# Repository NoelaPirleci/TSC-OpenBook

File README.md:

# TSC-OpenBook
# Descriere funcționalitate hardware

Proiectul se bazează pe microcontroller-ul **ESP32-C6**, care gestionează comunicarea cu toate componentele externe și senzorii conectați. Acest microcontroller oferă conectivitate **Wi-Fi** și **Bluetooth**, dar și suport pentru interfetele **SPI**, **I2C** și **UART**. Este conectat la 3V3 printr-un regulator de tensiune **LDO**, care primește energie de la o baterie **Li-Po** de 3.7V. 

Afisarea informațiilor se face utilizând un **display E-Paper** conectat prin **interfața SPI**, care are un consum redus de energie, fiind activ doar la actualizările ecranului. Informațiile afișate vor include data, ora, valorile senzorilor etc. 

Monitorizarea mediului se face cu ajutorul senzorului **BME688**, care măsoară temperatura, umiditatea și presiunea atmosferică, comunicând cu microcontroller-ul prin magistrala **I2C**. Modulul **RTC DS3231** este conectat și el la I2C și menține ora și data exactă, chiar și atunci când sistemul este oprit.

Prin **portul USB-C** se face alimentarea sistemului, care este conectat la circuitul de încărcare a bateriei utilizând **MCP73831**. Acesta controlează încărcarea bateriei Li-Po. Tensiunea va fi stabilită la **3.3V** pentru alimentarea senzorilor și a microcontroller-ului. Circuitul **MAX17048** este folosit pentru a monitoriza nivelul încărcării bateriei și furnizează informații despre tensiune și starea de încărcare prin I2C.

Consumul de energie este gestionat de ESP32-C6, care poate intra în **modul de consum redus**, permițând o durată lungă de viață a bateriei. Consumul în regim activ variază în funcție de sarcinile și componentele active în acel moment.

Pentru stocare, sistemul va folosi o **memorie externă NOR Flash**, conectată prin **SPI**, dar va exista și un slot pentru **card SD**, care va fi folosit pentru a loga local datele. Butoanele sunt conectate la **GPIO-uri** și vor fi folosite pentru resetare, bootare și alte acțiuni.

---

# Schema bloc

# Descriere pini ESP32-C6

Pinii microcontroller-ului **ESP32-C6** sunt utilizați în cadrul a cinci categorii:

## 1. Interfața SPI
Este folosită pentru comunicarea componentelor care necesită viteze mari de transfer. Pinii utilizați sunt:
- **IO0**: linia **MOSI** unde microcontroller-ul va trimite date către perifericele SPI.
- **IO1**: linia **MISO** unde ESP32-C6 va primi date de la cardul SD.
- **IO2**: linia **SCK** care va genera semnalul de ceas pentru sincronizarea SPI.
- **IO3**: linia **CS** pentru memoria **Flash NOR**.
- **IO4**: linia **CS** pentru display-ul **E-paper**.
- **IO5**: linia **CS** pentru slotul de card **SD**.
- **IO6, IO7, IO8**: pentru semnalele de control ale **E-Paper**-ului: **reset**, **busy**, **data/command (DC)**. Acești pini sunt utilizați pentru a evita conflictele cu alte interfețe și permit o rutare eficientă a traseelor pe placă.

## 2. Interfața I2C
Este folosită pentru a conecta senzorii de mediu și circuitele de monitorizare a tensiunii sau a timpului. Această interfață va conecta componentele: **BME688**, **MAX17048**, **DS3231**. Pinii folosiți sunt:
- **IO15**: linia **SCL**, folosită pentru semnalul de ceas.
- **IO16**: linia **SDA**, care va transmite date bidirecțional între microcontroller și perifericele I2C. Acești pini sunt aleși pentru a nu se suprapune cu cei de la SPI sau UART și pentru a permite extinderea prin **Qwiic**.

## 3. Interfața UART
Este folosită pentru **debugging**, comunicare serială sau conectare la module externe. Pinii utilizați sunt:
- **IO17**: **TXD**, linia de ieșire a datelor de la ESP32 către PC sau consolă.
- **IO18**: **RXD**, linia de intrare a datelor către ESP32. Acești pini sunt utili în faza de dezvoltare pentru testare, dar pot fi folosiți și în aplicațiile finale, dacă UART nu este necesar.

## 4. Pini GPIO
Sunt folosiți pentru butoanele **boot**, **reset** sau **change**. Pinii utilizați sunt:
- **IO9**: este folosit pentru **BOOT** și permite intrarea în modul de programare.
- **EN**: este pinul hardware **RESET** al ESP32-C6.
- **IO10, IO11**: sunt utilizați pentru butoane suplimentare, care au diverse acțiuni în aplicație. Acești pini au fost aleși pentru că sunt disponibili în schema de referință ESP32-C6 și nu sunt partajați cu perifericele.

## 5. Alimentare
Pinii de alimentare sunt:
- **3V3**: este intrarea de alimentare stabilizată la 3.3V, provenind din regulatorul LDO alimentat de la bateria **Li-Po**.
- **GND**: conexiunea de masă.

# Bill of Materials

| CNT | VAL | Device | Package | Parts | PURCHASE | DATASHEET |
| --- | ----- | ------ | ------- | ----- | ------------ | ------------- |
| 1 |  | ADAFRUIT_LEDCHIP-LED0603 | 0603 | CHG_LED | https://www.digikey.com/en/products/detail/w%C3%BCrth-elektronik/150060RS75000/4489901 | https://www.we-online.com/components/products/datasheet/150060RS75000.pdf |
| 1 | 0.1uF/50V | ESP32_WROVER_EAGLE-LTSPICE_C0402 | 0402 | EPD_C3 | https://www.digikey.com/en/products/detail/samsung-electro-mechanics/CL05B104KB5NNNC/11696318 | https://weblib.samsungsem.com/mlcc/mlcc-ec-data-sheet.do?partNumber=CL05B104KB5NNN |
| 1 | 0.47 | ESP32_WROVER_EAGLE-LTSPICE_RR0402 | 0402 | R3 | https://www.digikey.com/en/products/detail/panasonic-electronic-components/ERJ-2BQJR47X/5647384 | https://industrial.panasonic.com/cdbs/www-data/pdf/RDN0000/AOA0000C313.pdf |
| 1 | 100K | ESP32_WROVER_EAGLE-LTSPICE_RR0402 | 0402 | R_PWRUSB | https://www.digikey.com/en/products/detail/panasonic-electronic-components/ERJ-2RKF1003X/192081 | https://industrial.panasonic.com/cdbs/www-data/pdf/RDA0000/AOA0000C304.pdf |
| 8 | 100nF | ESP32_WROVER_EAGLE-LTSPICE_C0402 | 0402 | C1, C2, C3_USB, C5, C7, C8, C9, C_DELAY | https://www.digikey.com/en/products/detail/samsung-electro-mechanics/CL05B104KP5NNNC/3886660 | https://mm.digikey.com/Volume0/opasdata/d220001/medias/docus/609/CL05B104KP5NNNC_Spec.pdf |
| 1 | 100uF | RCL_CPOL-EUCT3528 | 3528 | C_TANT | https://ro.mouser.com/ProductDetail/KEMET/T491B107M006AT?qs=U312oeP%2FpiHOgyk6KO2m0g%3D%3D | https://ro.mouser.com/datasheet/2/447/KEM_T2005_T491-3316937.pdf
| 16 | 10K | ESP32_WROVER_EAGLE-LTSPICE_RR0402 | 0402 | R1, R1_PINH1, R1_PINH2, R2-PINH1, R2_PINH2, R4, R5, R6, R7, R8, R9, R10, R_BOOT, R_CHANGE, R_CL1, R_RESET | https://www.digikey.com/en/products/detail/panasonic-electronic-components/ERJ-2RKF1002X/192073 | https://industrial.panasonic.com/cdbs/www-data/pdf/RDA0000/AOA0000C304.pdf |
| 1 | 10uF | ESP32_WROVER_EAGLE-LTSPICE_C0402 | 0402 | C6 | https://www.digikey.com/en/products/detail/samsung-electro-mechanics/CL05A106MP5NUNC/3887108 | https://mm.digikey.com/Volume0/opasdata/d220001/medias/docus/2614/CL05A106MP5NUNC_Spec.pdf |
| 1 | 112A-TAAR-R03_ATTEND | 112A-TAAR-R03_ATTEND |  | J4 | https://www.digikey.ro/en/products/detail/attend-technology/112A-TAAR-R03/17633923 | https://www.attend.com.tw/data/download/file/112A-TAAR-R03_Spec.pdf |
| 1 | 15 | ESP32_WROVER_EAGLE-LTSPICE_RR0402 | 0402 | R_CAPACITOR | https://www.digikey.com/en/products/detail/panasonic-electronic-components/ERJ-2RKF15R0X/192142 | https://industrial.panasonic.com/cdbs/www-data/pdf/RDA0000/AOA0000C304.pdf |
| 1 | 1uF | ESP32_WROVER_EAGLE-LTSPICE_C0402 | 0402 | C4 | https://www.digikey.com/en/products/detail/samsung-electro-mechanics/CL05A105KO5NNNC/3886725 | https://mm.digikey.com/Volume0/opasdata/d220001/medias/docus/609/CL05A105KO5NNNC_Spec_5-2-19.pdf |
| 9 | 1uF/50V | ESP32_WROVER_EAGLE-LTSPICE_C0402 | 0402 | EPD_C1, EPD_C2, EPD_C4, EPD_C5, EPD_C6, EPD_C7, EPD_C8, EPD_C9, EPD_C10 | https://www.digikey.com/en/products/detail/murata-electronics/GRM155R61H105KE05D/13531808 | https://search.murata.co.jp/Ceramy/image/img/A01X/G101/ENG/GRM155R61H105KE05-01A.pdf |
| 1 | 2.2 | ESP32_WROVER_EAGLE-LTSPICE_RR0402 | 0402 | R2 | https://www.digikey.com/en/products/detail/panasonic-electronic-components/ERJ-2GEJ2R2X/282078 | https://api.pim.na.industrial.panasonic.com/file_stream/main/fileversion/1242 |
| 1 | 200 | ESP32_WROVER_EAGLE-LTSPICE_RR0402 | 0402 | R1_BAT | https://www.digikey.com/en/products/detail/panasonic-electronic-components/ERJ-2RKF2000X/192215 | https://industrial.panasonic.com/cdbs/www-data/pdf/RDA0000/AOA0000C304.pdf |
| 2 | 20V/4.2A/52mO/1.4W | ESP32_WROVER_SPARKFUN-DISCRETESEMI_MOSFET_PCH-DMG2305UX-7 |  | Q1, Q2 | https://www.digikey.ro/en/products/detail/diodes-incorporated/DMG2305UX-7/4340667 | https://www.diodes.com/assets/Datasheets/DMG2305UX.pdf |
| 1 | 2K | ESP32_WROVER_EAGLE-LTSPICE_RR0402 | 0402 | R2_BAT | https://www.digikey.com/en/products/detail/panasonic-electronic-components/ERJ-2RKF2001X/192194 | https://industrial.panasonic.com/cdbs/www-data/pdf/RDA0000/AOA0000C304.pdf |
| 5 | 4.7uF | ESP32_WROVER_EAGLE-LTSPICE_C0402 | 0402 | C1_BAT, C1_BAT1, C2_BAT, C2_BAT1, C4_USB | https://www.digikey.com/en/products/detail/samsung-electro-mechanics/CL05A475KQ5NRNC/3887139 | https://mm.digikey.com/Volume0/opasdata/d220001/medias/docus/41/CL05A475KQ5NRNC_Spec.pdf |
| 1 | 4.7uF/25V | ESP32_WROVER_EAGLE-LTSPICE_C0402 | 0402 | C3 | https://www.digikey.com/en/products/detail/murata-electronics/GRM155C61E475ME15D/16821133 | https://search.murata.co.jp/Ceramy/image/img/A01X/G101/ENG/GRM155C61E475ME15-01A.pdf |
| 2 | 5k1 | ESP32_WROVER_EAGLE-LTSPICE_RR0402 | 0402 | R1_USB, R2_USB | https://www.digikey.com/en/products/detail/panasonic-electronic-components/ERJ-2GEJ512X/147044 | https://api.pim.na.industrial.panasonic.com/file_stream/main/fileversion/1242 |
| 1 | 68uH | 744043680IND_4828-WE-TPC_WRE |  | L1 | https://www.digikey.de/en/products/detail/w%C3%BCrth-elektronik/744043680/1638515?srsltid=AfmBOoreM6iTR1zfidcAYx5855uFKN_t-1dK5Y4hJLHk64FUsesZV3qH | https://www.we-online.com/components/products/datasheet/744043680.pdf |
| 1 | BD5229G-TR | BD5229G-TR |  | U6 | https://www.digikey.com/en/products/detail/rohm-semiconductor/BD5229G-TR/658502 | https://www.rohm.com/datasheet?p=BD5229G&dist=Digi-key&media=referral&source=digi-key.com&campaign=Digi-key |
| 1 | BME688 | ESP32_WROVER_BME680_BME680 |  | U8 | https://www.digikey.ro/en/products/detail/bosch-sensortec/BME688/13681261 | https://www.bosch-sensortec.com/media/boschsensortec/downloads/datasheets/bst-bme688-ds000.pdf |
| 3 | BUTTON_CUSYOMV1 | BUTTON_CUSYOMV1 |  | BOOT_BUTTON, CHANGE_BUTTON, RESET_BUTTON |  |  |
| 1 | CPH3225A | CPH3225A |  | C_SUPERCAP | https://www.digikey.com/en/products/detail/seiko-instruments/CPH3225A/8692444 | https://mm.digikey.com/Volume0/opasdata/d220001/medias/docus/6537/rev05-CPHCPM.pdf |
| 1 | DS3231SN# | DS3231SN# |  | U3 | https://www.digikey.com/en/products/detail/analog-devices-inc-maxim-integrated/DS3231SN/1197576 | https://www.analog.com/media/en/technical-documentation/data-sheets/DS3231.pdf |
| 1 | ESP32-C6-WROOM-1-N8 | ESP32-C6-WROOM-1-N8 |  | U1 | https://www.digikey.com/en/products/detail/espressif-systems/ESP32-C6-WROOM-1-N8/17728866 | https://www.espressif.com/sites/default/files/documentation/esp32-c6-wroom-1_wroom-1u_datasheet_en.pdf |
| 1 | ESP32C6_VARISTORCN1812 | ESP32C6_VARISTORCN1812 |  | PFMF.050.1 | https://www.digikey.com/en/products/detail/schurter-inc/PFMF-050-2/1731348 | https://us.schurter.com/en/datasheet/typ_PFMF.pdf |
| 2 | ESP32_WROVER_AVX---SD0805S020S1R0 | ESP32_WROVER_AVX---SD0805S020S1R0 |  | D2, D7 | https://www.digikey.gr/en/products/detail/kyocera-avx/SD0805S020S1R0/3749517 | https://datasheets.kyocera-avx.com/schottky.pdf |
| 1 | FH34SRJ-24S-0.5SH_99_ | FH34SRJ-24S-0.5SH_99_ |  | J1 | https://www.digikey.com/en/products/detail/hirose-electric-co-ltd/FH34SRJ-24S-0-5SH-99/5132529 | https://www.hirose.com/en/product/document?clcode=CL0580-1253-0-99&productname=FH34SRJ-12S-0.5SH(99)&series=FH34SRJ&documenttype=SpecSheet&lang=en&documentid=0000414526 |
| 1 | MAX17048G+T10 | MAX17048G+T10 |  | U2 | https://www.digikey.com/en/products/detail/analog-devices-inc-maxim-integrated/MAX17048G-T10/3758921 | https://datasheets.maximintegrated.com/en/ds/MAX17048-MAX17049.pdf |
| 3 | MBR0530 | MBR0530 |  | D3, D4, D5 | https://eu.mouser.com/ProductDetail/Micro-Commercial-Components-MCC/MBR0530-TP?qs=KFo7JewZbUECRHkxGanrdg%3D%3D&srsltid=AfmBOopI5EY-Qmh6fu8QJtXckZ14Imu1WB2G5-0En3D3mZ6aqi4jmsQ2 | https://eu.mouser.com/datasheet/2/258/MBR0520_MBR0580_SOD123_-2492194.pdf |
| 1 | MCP73831 | ESP32_WROVER_SPARKFUN-IC-POWER_MCP73831 |  | U7 | https://www.digikey.com/en/products/detail/microchip-technology/MCP73831T-2ACI-OT/964301 | https://ww1.microchip.com/downloads/en/DeviceDoc/MCP73831-Family-Data-Sheet-DS20001984H.pdf |
| 6 | PGB1010603MR | PGB1010603MR |  | D6, D8, D9, D10, D11, D12 | https://www.digikey.com/en/products/detail/littelfuse-inc/PGB1010603MR/715755 | https://www.littelfuse.com/assetdocs/pulseguard-esd-suppressors-pgb1-datasheet?assetguid=8a337998-d54d-466b-be4e-dc5bcd1f9321 |
| 1 | QWIIC_RIGHT_ANGLE | QWIIC_CONNECTORJS-1MM |  | J3 | https://www.sparkfun.com/qwiic-jst-connector-smd-4-pin-horizontal.html | https://cdn.sparkfun.com/assets/parts/1/2/2/8/9/Qwiic_Connector_Datasheet.pdf |
| 1 | SAMACSYS_PARTS_USB4110-GF-A | SAMACSYS_PARTS_USB4110-GF-A |  | J2 | https://www.digikey.ro/en/products/detail/gct/USB4110-GF-A/10384547 | https://gct.co/files/specs/usb4110-spec.pdf?v=6b2a6292-70a5-4bd5-a7e5-0f3fe03e015f |
| 1 | SI1308EDL-T1-GE3 | SI1308EDL-T1-GE3 |  | Q3 | https://www.digikey.com/en/products/detail/vishay-siliconix/SI1308EDL-T1-GE3/4876435 | https://www.vishay.com/docs/63399/si1308edl.pdf |
| 1 | USBLC6-2SC6Y | USBLC6-2SC6Y |  | D1 | https://www.digikey.com/en/products/detail/stmicroelectronics/USBLC6-2SC6Y/2819177 | https://www.st.com/content/ccc/resource/technical/document/datasheet/group0/94/15/6c/58/ba/91/46/42/DM00055262/files/DM00055262.pdf/jcr:content/translations/en.DM00055262.pdf |
| 1 | W25Q512JVEIQ | W25Q512JVEIQ |  | U4 | https://www.digikey.com/en/products/detail/winbond-electronics/W25Q512JVEIQ/10244706 | https://www.winbond.com/resource-files/W25Q512JV%20SPI%20RevB%2006252019%20KMS.pdf |
| 1 | XC6220A331MR-G | XC6220A331MR-G |  | U5 | https://www.digikey.in/en/products/detail/torex-semiconductor-ltd/XC6220A331MR-G/10165775 | https://product.torexsemi.com/system/files/series/xc6220.pdf |

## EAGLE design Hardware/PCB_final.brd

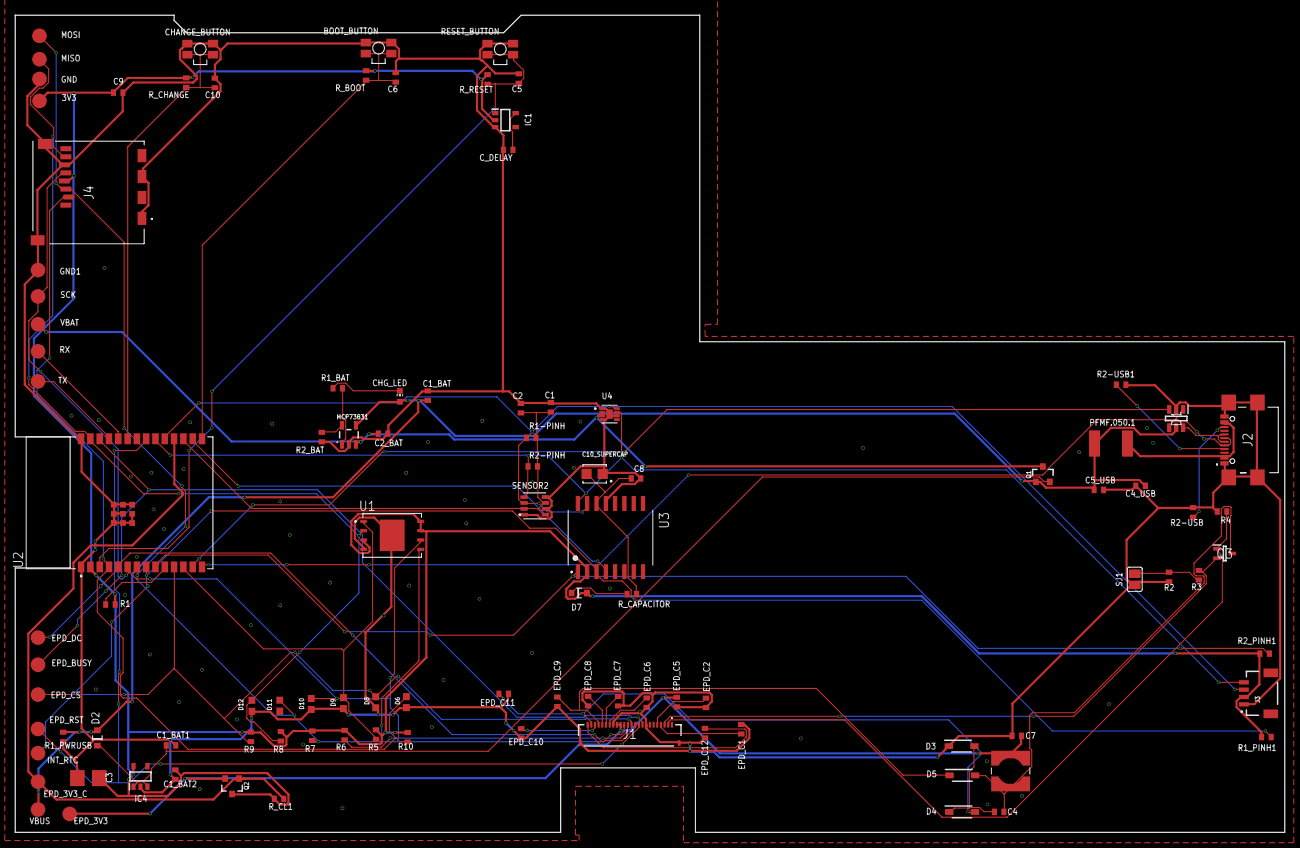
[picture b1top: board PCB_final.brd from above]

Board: 2 copper layers, 173.4 x 111.6 mm, 103 parts (0 on the bottom side), 55 nets.

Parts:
3V3: TPMODEL; TP20R
BOOT_BUTTON: BUTTON_CUSYOMV1BUTON; MYBUTTON
C1, C2, C4_USB, C6, C8, C9, C10: 100nF; ESP32_WROVER_EAGLE-LTSPICE_C0402
C1_BAT, C1_BAT1, C1_BAT2, C2_BAT, C5_USB: 4.7uF; ESP32_WROVER_EAGLE-LTSPICE_C0402
C3: 100uF TANT; RCL_CT3528
C4: 4.7uF/25V; ESP32_WROVER_EAGLE-LTSPICE_C0402
C5: 1uF; ESP32_WROVER_EAGLE-LTSPICE_C0402
C7: 10uF; ESP32_WROVER_EAGLE-LTSPICE_C0402
C10_SUPERCAP: CPH3225ASUPERCAP; CAPCP3225X100N
CHANGE_BUTTON: BUTTON_CUSYOMV1BUTON; MYBUTTON
CHG_LED: ADAFRUIT_CHIP-LED0603
C_DELAY: 100nF; ESP32_WROVER_EAGLE-LTSPICE_C0402
D1: USBLC6-2SC6YUSBL; SOT95P280X145-6N
D2, D7: ESP32_WROVER_AVX---SD0805S020S1R0_AVX_SD0805S020S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; ESP32_WROVER_AVX---SD0805S020S1R0_AVX_SD0805S020S1R0_0
D3, D4, D5: MBR0530MBR; SOD3716X135N
D6, D8, D9, D10, D11, D12: PGB1010603MRDIOC; DIOC1608X36N
EPD_3V3, EPD_3V3_C: TPMODEL; TP20R
EPD_BUSY: TPMODEL; TP20R
EPD_C1, EPD_C2, EPD_C5, EPD_C6, EPD_C7, EPD_C8, EPD_C9, EPD_C10, EPD_C11, EPD_C12: 1uF/50V; ESP32_WROVER_EAGLE-LTSPICE_C0402
EPD_CS: TPMODEL; TP20R
EPD_DC: TPTP20R; TP20R
EPD_RST: TPMODEL; TP20R
GND, GND1: TPTP20R; TP20R
IC1: BD5229G-TRBD5229; SOT95P280X125-5N
IC4: XC6220A331MR-G; SOT95P280X120-5N
INT_RTC: TPMODEL; TP20R
J1: FH34SRJ-24S-0.5SH_99_FH34; FH34SRJ24S05SH99
J2: SAMACSYS_PARTS_USB4110-GF-AUSB; SAMACSYS_PARTS_USB4110GFA
J3: QWIIC_RIGHT_ANGLE; JST04_1MM_RA
J4: 112A-TAAR-R03_ATTENDSDCARD; 112ATAARR03ATTEND
L1: 68uH; IND_4828-WE-TPC_WRE
MCP73831: ESP32_WROVER_SPARKFUN-IC-POWER_MCP73831ICPOWER; ESP32_WROVER_SPARKFUN-IC-POWER_SOT23-5
MISO: TPTP20R; TP20R
MOSI: TPMODEL; TP20R
PFMF.050.1: ESP32C6_VARISTOR; ESP32C6_VARISTOR_CT/CN1812
Q1, Q2: 20V/4.2A/52mΩ/1.4W; ESP32_WROVER_SPARKFUN-DISCRETESEMI_SOT23-3
Q3: SI1308EDL-T1-GE3SI13; SOT65P210X110-3N
R1, R1-PINH, R1_PINH1, R2-PINH, R2_PINH1, R4, R5, R6, R7, R8, R9, R10: 10K; ESP32_WROVER_EAGLE-LTSPICE_R0402
R1_BAT: 200; ESP32_WROVER_EAGLE-LTSPICE_R0402
R1_PWRUSB: 100K; ESP32_WROVER_EAGLE-LTSPICE_R0402
R2: 2.2; ESP32_WROVER_EAGLE-LTSPICE_R0402
R2-USB, R2-USB1: 5k1; ESP32_WROVER_EAGLE-LTSPICE_R0402
R2_BAT: 2K; ESP32_WROVER_EAGLE-LTSPICE_R0402
R3: 0.47; ESP32_WROVER_EAGLE-LTSPICE_R0402
RESET_BUTTON: BUTTON_CUSYOMV1BUTON; MYBUTTON
RX: TPMODEL; TP20R
R_BOOT: 10K; ESP32_WROVER_EAGLE-LTSPICE_R0402
R_CAPACITOR: 15; ESP32_WROVER_EAGLE-LTSPICE_R0402
R_CHANGE: 10K; ESP32_WROVER_EAGLE-LTSPICE_R0402
R_CL1: 10K; ESP32_WROVER_EAGLE-LTSPICE_R0402
R_RESET: 10K; ESP32_WROVER_EAGLE-LTSPICE_R0402
SCK: TPMODEL; TP20R
SENSOR2: ESP32_WROVER_BME680_BME680BME; ESP32_WROVER_BME680_PSON80P300X300X100-8N
SJ1: SJ
TX: TPMODEL; TP20R
U1: W25Q512JVEIQ"; SON127P600X800X80-9N
U2: ESP32-C6-WROOM-1-N8; XCVR_ESP32-C6-WROOM-1-N8
U3: DS3231SN#DS3231; SOIC127P1032X265-16N
U4: MAX17048G+T10MAX170; SON50P200X200X80-9N
VBAT: TPMODEL; TP20R
VBUS: TPTP20R; TP20R

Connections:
3V3: 3V3.TP, C1_BAT2.1, C3.+, C9.1, D7.2, IC1.2, IC4.5, J3.2, J4.P4, Q2.3, R1.2, R1_PINH1.2, R2_PINH1.2, R5.2, R6.2, R7.2, R8.2, R9.2, R10.2, R_BOOT.2, R_CHANGE.2, R_CL1.2, R_RESET.2, U1.3, U1.7, U1.8, U2.2, U3.2
32KHZ: R2_PINH1.1, U2.9, U3.1
DN: D1.4, J2.A7, J2.B7
DP: D1.6, J2.A6, J2.B6
EPD_3V3: C7.1, EPD_3V3.TP, EPD_C5.2, J1.15, J1.16, L1.2, Q2.2
EPD_3V3_C: EPD_3V3_C.TP, Q2.1, R_CL1.1, U2.18
EPD_BUSY: EPD_BUSY.TP, J1.9, U2.26
EPD_CS: D8.2, EPD_CS.TP, J1.12, R9.1, U2.11
EPD_DC: EPD_DC.TP, J1.11, U2.5
EPD_RST: EPD_RST.TP, J1.10, U2.21
FLASH_CS: D9.2, R5.1, U1.1, U2.12
GDR: J1.2, Q3.1, R4.2
GND: BOOT_BUTTON.1, BOOT_BUTTON.2, C1.2, C1_BAT.2, C1_BAT1.2, C1_BAT2.2, C2.2, C2_BAT.2, C3.-, C4_USB.2, C5.2, C5_USB.2, C6.2, C7.2, C8.2, C9.2, C10.2, C10_SUPERCAP.1, CHANGE_BUTTON.1, CHANGE_BUTTON.2, C_DELAY.2, D1.2, D3.1, D6.1, D8.1, D9.1, D10.1, D12.1, EPD_C1.1, EPD_C2.1, EPD_C5.1, EPD_C6.1, EPD_C7.1, EPD_C8.1, EPD_C9.1, EPD_C10.1, EPD_C11.1, EPD_C12.1, GND.TP, GND1.TP, IC1.3, IC4.2, J1.8, J1.17, J1.MP1, J1.MP2, J2.A1, J2.A12, J2.B1, J2.B12, J2.MP1, J2.MP2, J2.MP3, J2.MP4, J3.1, J4.G1, J4.G2, J4.G3, J4.G4, J4.P6, MCP73831.2, R1_PWRUSB.1, R2.1, R2-USB.2, R2-USB1.1, R2_BAT.1, R4.1, RESET_BUTTON.1, RESET_BUTTON.2, SENSOR2.1, SENSOR2.5, SENSOR2.7, SJ1.1, U1.4, U1.9, U2.1, U2.28, U2.29_1, U2.29_2, U2.29_3, U2.29_4, U2.29_5, U2.29_6, U2.29_7, U2.29_8, U2.29_9, U3.13, U4.1, U4.4, U4.6, U4.9
GPIO8: R1.1, U2.10
I2C_PW: C1.1, C2.1, R1-PINH.2, R2-PINH.2, SENSOR2.2, SENSOR2.6, SENSOR2.8, U2.17
INT_RTC: INT_RTC.TP, R1_PINH1.1, U2.8, U3.3
IO/BOOT: BOOT_BUTTON.3, BOOT_BUTTON.4, C6.1, R_BOOT.1, U2.15
IO/CHANGE: C10.1, CHANGE_BUTTON.3, CHANGE_BUTTON.4, R_CHANGE.1, U2.23
MISO: D12.2, J4.P7, MISO.TP, R8.1, U1.2, U2.27
MOSI: D11.2, J1.14, J4.P3, MOSI.TP, R7.1, U1.5, U2.7
unnamed: J2.B5, R2-USB.1
unnamed: J2.A5, R2-USB1.2
unnamed: C1_BAT1.1, D2.1, IC4.1, IC4.3, Q1.2
unnamed: C4.1, D3.2, D4.1
unnamed: CHG_LED.C, R1_BAT.1
unnamed: MCP73831.1, R1_BAT.2
unnamed: MCP73831.5, R2_BAT.2
unnamed: EPD_C12.2, J1.24
unnamed: EPD_C8.2, J1.20
unnamed: EPD_C10.2, J1.22
unnamed: EPD_C7.2, J1.19
unnamed: EPD_C6.2, J1.18
unnamed: EPD_C2.2, J1.5
unnamed: EPD_C1.2, J1.4
unnamed: C_DELAY.1, IC1.5
unnamed: D7.1, R_CAPACITOR.1
PREVGH: D5.1, EPD_C9.2, J1.21
PREVGL: D4.2, EPD_C11.2, J1.23
RESE: J1.3, Q3.2, R3.2
RESE': R2.2, R3.1, SJ1.2
RESET: C5.1, IC1.1, RESET_BUTTON.3, RESET_BUTTON.4, R_RESET.1, U2.3
RTC_RST: U2.16, U3.4
RX: RX.TP, U2.24
SCK: D10.2, J1.13, J4.P5, R6.1, SCK.TP, U1.6, U2.6
SCL: J3.4, R2-PINH.1, SENSOR2.4, U2.20, U3.16, U4.7
SDA: J3.3, R1-PINH.1, SENSOR2.3, U2.19, U3.15, U4.8
SRC: C4.2, D5.2, L1.1, Q3.3
SS_SD: D6.2, J4.P2, R10.1, U2.4
TX: TX.TP, U2.25
USB_D+: D1.1, U2.14
USB_D-: D1.3, U2.13
VBAT: C2_BAT.1, MCP73831.3, Q1.3, U4.2, U4.3, VBAT.TP
VBUS: C1_BAT.1, C4_USB.1, C5_USB.1, CHG_LED.A, D1.5, D2.2, MCP73831.4, PFMF.050.1.2, Q1.1, R1_PWRUSB.2, VBUS.TP
VRTC: C8.1, C10_SUPERCAP.2, R_CAPACITOR.2, U3.14
VUSB: J2.A4, J2.A9, J2.B4, J2.B9, PFMF.050.1.1

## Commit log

2025-04-06 Create test
2025-04-06 Added PCB.
2025-04-06 Create Manufacturing folder.
2025-04-06 Added Gerber Files.
2025-04-06 Added Bill of Materials.
2025-04-06 Added Pick and Place file.
2025-04-06 Create Mechanical folder.
2025-04-06 Add 3D model.
2025-04-06 Add exploded view.
2025-04-06 Add exploded view for 3D model.
2025-04-06 Create Images folder.
2025-04-06 Add exploded view image.
2025-04-06 Add image with the product.
2025-04-06 Added another image with the product.
2025-04-06 Add LICENSE.
2025-04-06 Add the scheme.
2025-04-06 Add README.
2025-04-14 Add final electric schematic.
2025-04-14 Add final PCB board design.
2025-04-14 Remove old PCB.
2025-04-14 Add the model for the whole e-book.
